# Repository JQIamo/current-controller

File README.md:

# Low noise current controller

Gerber files for a low-noise current controller, based on the design from the Durfee lab. [DOI:10.1063/1.2953597](http://scitation.aip.org/content/aip/journal/rsi/79/7/10.1063/1.2953597)

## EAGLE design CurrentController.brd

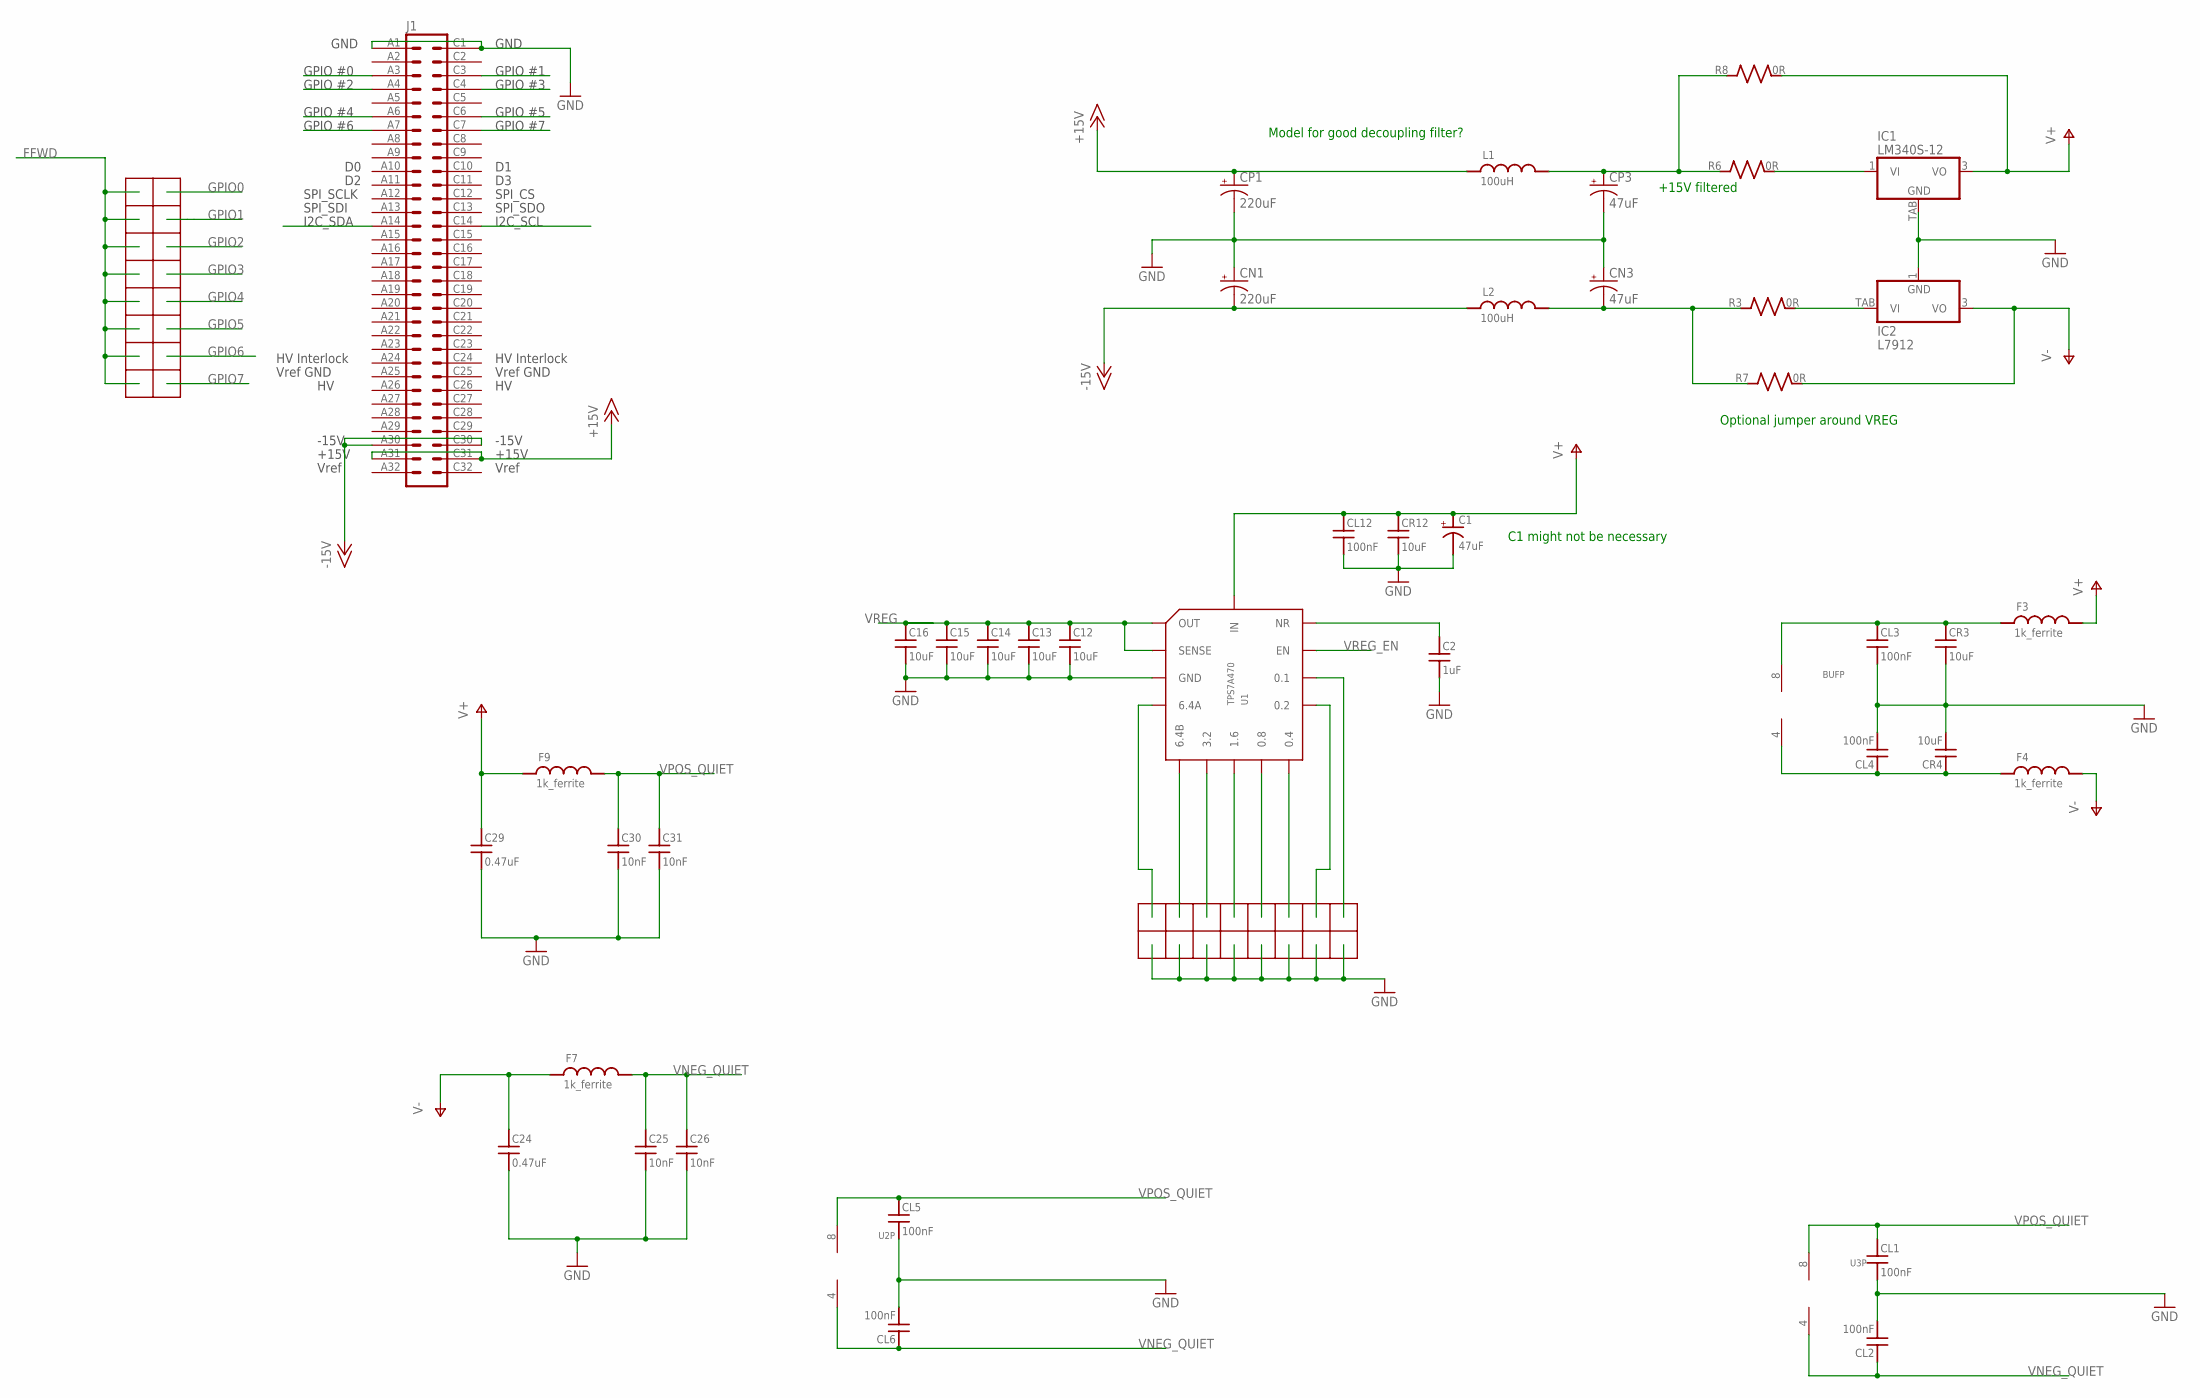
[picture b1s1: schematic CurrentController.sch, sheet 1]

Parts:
BUF: AD8676; MSOP08; PARTNO AD8676ARMZ
C1: 47uF; C_POL_1206
C2: 1uF; C_MLCC_0603; PARTNO CL10B105KA8NNNC
C12, C13, C14, C15, C16: 10uF; C_MLCC_0805; PARTNO CL21A106KAFN3NE
C24, C29: 0.47uF; C_MLCC_0612; PARTNO LLL31MR71E474MA01L
C25, C26, C30, C31: 10nF; C_MLCC_0306; PARTNO 03063C103KAT2A
CL1, CL2, CL3, CL4, CL5, CL6, CL12: 100nF; C_MLCC_0603; PARTNO C1608X7R1E104K080AA
CN1: 220uF; PANASONIC_F; PARTNO EEE-1VA221UP
CN3: 47uF; CT7343; PARTNO T491D476M025AT
CP1: 220uF; PANASONIC_F; PARTNO EEE-1VA221UP
CP3: 47uF; CT7343; PARTNO T491D476M025AT
CR3, CR4, CR12: 10uF; C_MLCC_0805; PARTNO CL21A106KAFN3NE
F3, F4, F7, F9: 1k_ferrite; L_FERRITE_0603; PARTNO BLM18HG102SN1D
IC1: LM340S-12; TO263-3; PARTNO LM340S-12/NOPB
IC2: L7912; TO223-3; PARTNO MC7912CD2TG
J1: VG64C; VG64-CUTOUT; PARTNO 5650945-5
J2, J3: 2X8_LOW_PROFILE_JUMPER; 2X8_LOW_PROFILE_JUMPER_MATRIX; PARTNO A3B-16PA-2DSA(71)
L1, L2: 100uH; WURTH_1280; PARTNO 74477020
R3, R6, R7, R8: 0R; R_1206; PARTNO ERJ-8GEY0R00V
U1: TPS7A470; S-PVQFN-N20; PARTNO TPS7A4701RGWT
U2, U3: AD8676; MSOP08; PARTNO AD8676ARMZ

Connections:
+15V: CP1.+, J1.A31, J1.C31, L1.P$1 (1)
-15V: CN1.-, J1.A30, J1.C30, L2.P$1 (1)
FFWD: J2.P$1, J2.P$3, J2.P$5, J2.P$7, J2.P$9, J2.P$11, J2.P$13, J2.P$15; also elsewhere on the board
GND: C1.P$2 (-), C2.P$2 (2), C12.P$2 (2), C13.P$2 (2), C14.P$2 (2), C15.P$2 (2), C16.P$2 (2), C24.P$2 (2), C25.P$2 (2), C26.P$2 (2), C29.P$2 (2), C30.P$2 (2), C31.P$2 (2), CL1.P$2 (2), CL2.P$2 (2), CL3.P$2 (2), CL4.P$2 (2), CL5.P$2 (2), CL6.P$2 (2), CL12.P$2 (2), CN1.+, CN3.+, CP1.-, CP3.-, CR3.P$2 (2), CR4.P$2 (2), CR12.P$2 (2), IC1.TAB (GND), IC2.1 (GND), J1.A1, J1.C1, J3.P$1, J3.P$3, J3.P$5, J3.P$7, J3.P$9, J3.P$11, J3.P$13, J3.P$15, U1.2 (GND), U1.7 (GND), U1.17 (GND), U1.18 (GND), U1.19 (GND), U1.EXP (GND); also elsewhere on the board
GPIO0: J1.A3, J2.P$2
GPIO1: J1.C3, J2.P$4
GPIO2: J1.A4, J2.P$6
GPIO3: J1.C4, J2.P$8
GPIO4: J1.A6, J2.P$10
GPIO5: J1.C6, J2.P$12
GPIO6: J1.A7, J2.P$14
GPIO7: J1.C7, J2.P$16
unnamed: J3.P$2, U1.4 (6.4A)
unnamed: IC2.TAB (VI), R3.P$2 (2)
unnamed: IC1.1 (VI), R6.P$2 (2)
unnamed: J3.P$4, U1.5 (6.4B)
unnamed: CN3.-, L2.P$2 (2), R3.P$1 (1), R7.P$1 (1)
unnamed: J3.P$6, U1.6 (3.2)
unnamed: CP3.+, L1.P$2 (2), R6.P$1 (1), R8.P$1 (1)
unnamed: J3.P$8, U1.8 (1.6)
unnamed: BUF.4 (V-), CL4.P$1 (1), CR4.P$1 (1), F4.P$1 (1)
unnamed: BUF.8 (V+), CL3.P$1 (1), CR3.P$1 (1), F3.P$1 (1)
unnamed: J3.P$10, U1.9 (0.8)
unnamed: J3.P$12, U1.10 (0.4)
unnamed: J3.P$14, U1.11 (0.2)
unnamed: J3.P$16, U1.12 (0.1)
unnamed: C2.P$1 (1), U1.14 (NR)
SCL: J1.C14; also elsewhere on the board
SDA: J1.A14; also elsewhere on the board
V+: C1.P$1 (+), C29.P$1 (1), CL12.P$1 (1), CR12.P$1 (1), F3.P$2 (2), F9.P$1 (1), IC1.3 (VO), R8.P$2 (2), U1.15 (IN), U1.16 (IN); also elsewhere on the board
V-: C24.P$1 (1), F4.P$2 (2), F7.P$1 (1), IC2.3 (VO), R7.P$2 (2); also elsewhere on the board
VNEG_QUIET: C25.P$1 (1), C26.P$1 (1), CL2.P$1 (1), CL6.P$1 (1), F7.P$2 (2), U2.4 (V-), U3.4 (V-); also elsewhere on the board
VPOS_QUIET: C30.P$1 (1), C31.P$1 (1), CL1.P$1 (1), CL5.P$1 (1), F9.P$2 (2), U2.8 (V+), U3.8 (V+); also elsewhere on the board
VREG: C12.P$1 (1), C13.P$1 (1), C14.P$1 (1), C15.P$1 (1), C16.P$1 (1), U1.1 (OUT), U1.3 (SENSE), U1.20 (OUT); also elsewhere on the board
VREG_EN: U1.13 (EN); also elsewhere on the board

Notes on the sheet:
+15V filtered
Optional jumper around VREG
Model for good decoupling filter?
C1 might not be necessary

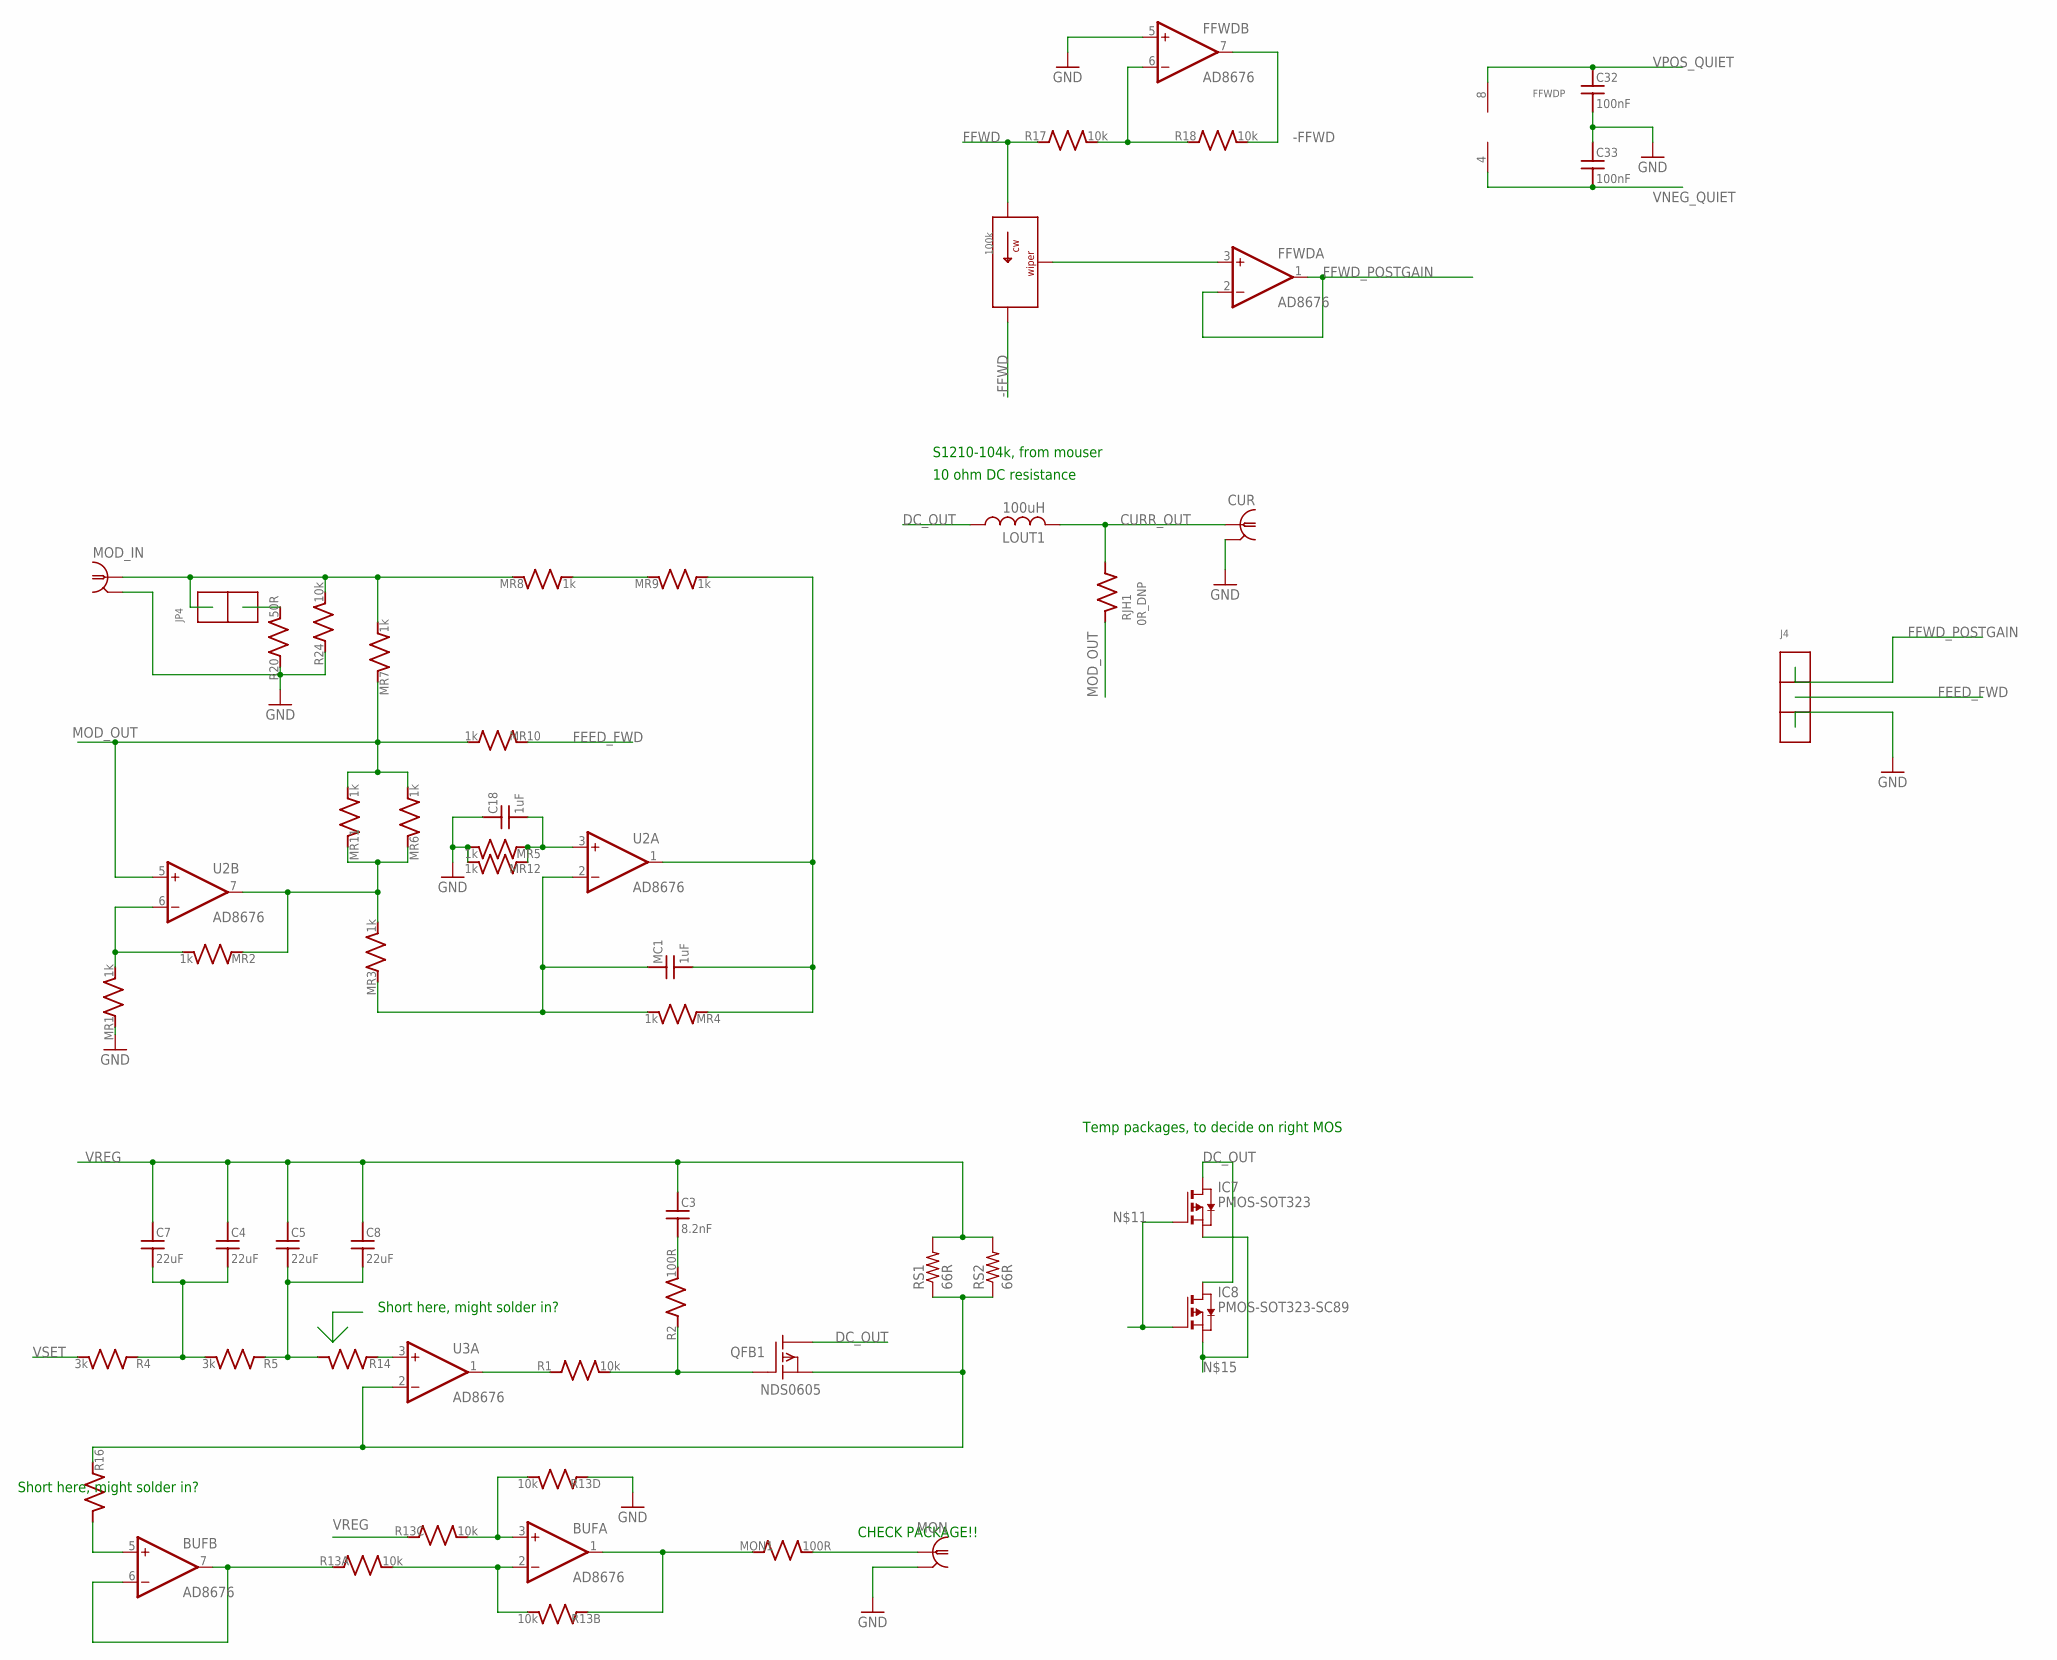
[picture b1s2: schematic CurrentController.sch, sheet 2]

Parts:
BUF: AD8676; MSOP08; PARTNO AD8676ARMZ
C3: 8.2nF; C_MLCC_0603; PARTNO CL10B822KB8NNNC
C4, C5, C7, C8: 22uF; C_MLCC_0805; PARTNO C2012X5R1E226M125AC
C18: 1uF; C_MLCC_0603; PARTNO CL10B105KA8NNNC
C32, C33: 100nF; C_MLCC_0603; PARTNO C1608X7R1E104K080AA
CUR: BNC-H; BNC90; PARTNO 5227161-7
FFWD: AD8676; MSOP08; PARTNO AD8676ARMZ
IC7: PMOS-SOT323; SOT323
IC8: PMOS-SOT323-SC89; SC-89
J4: 1X3_LOW_PROFILE_JUMPER; 1X3_LOW_PROFILE; PARTNO NRPN031PAEN-RC
JP4: 1X2_LOW_PROFILE_JUMPER; 1X2_LOW_PROFILE; PARTNO NRPN021PAEN-RC
LOUT1: 100uH; L3225P; PARTNO CBC3225T680KR
MC1: 1uF; C_MLCC_0603; PARTNO CL10B105KA8NNNC
MOD_IN: BNC-H; BNC90; PARTNO 5227161-7
MON: UMC; PARTNO 1909763-1
MON1: 100R; R_0603; PARTNO ERJ-3EKF1000V
MR1, MR2, MR3, MR4, MR5, MR6, MR7, MR8, MR9, MR10, MR11, MR12: 1k; R_0805; PARTNO ERA-6ARB102V
QFB1: NDS0605; SOT-23; PARTNO *
R1, R17, R18, R24: 10k; R_0603; PARTNO ERJ-3EKF1002V
R2: 100R; R_0603; PARTNO ERJ-3EKF1000V
R4, R5: 3k; R_0603; PARTNO ERJ-3EKF3001V
R13: 10k; 742_ARRAY; PARTNO 742C083103JP
R14, R16: R_SMDR0603; R_0603
R20: 50R; R_0805; PARTNO ERJ-6ENF49R9V
RJH1: 0R_DNP; R_0603
RS1, RS2: 66R; R2010
T1: 100k; 3006P; PARTNO 3006P-1-104LF
U2, U3: AD8676; MSOP08; PARTNO AD8676ARMZ

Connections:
-FFWD: FFWD.7 (OUT), R18.P$2 (2), T1.P$3
CURR_OUT: CUR.1, LOUT1.2, RJH1.P$1 (1)
DC_OUT: IC7.3 (D), IC8.P$3 (D), LOUT1.1, QFB1.3 (D)
FEED_FWD: J4.P2, MR10.P$1 (1)
FFWD: R17.P$1 (1), T1.P$1; also elsewhere on the board
FFWD_POSTGAIN: FFWD.1 (OUT), FFWD.2 (-IN), J4.P1
GND: C18.P$1 (1), C32.P$2 (2), C33.P$1 (1), CUR.2, FFWD.5 (+IN), J4.P3, MOD_IN.2, MON.P$2 (2), MON.P$3 (2), MR1.P$1 (1), MR5.P$2 (2), MR12.P$2 (2), R13.P$7 (1), R20.P$1 (1), R24.P$1 (1); also elsewhere on the board
MODIN_B: JP4.1, MOD_IN.1, MR7.P$2 (2), MR8.P$1 (1), R24.P$2 (2)
MOD_OUT: MR6.P$2 (2), MR7.P$1 (1), MR10.P$2 (2), MR11.P$2 (2), RJH1.P$2 (2), U2.5 (+IN)
MON: BUF.1 (OUT), MON1.P$1 (1), R13.P$3 (1)
MON_MON: MON.P$1 (1), MON1.P$2 (2)
unnamed: MR8.P$2 (2), MR9.P$1 (1)
unnamed: BUF.6 (-IN), BUF.7 (OUT), R13.P$1 (1)
unnamed: BUF.5 (+IN), R16.P$2 (2)
unnamed: FFWD.3 (+IN), T1.P$2
unnamed: C4.P$2 (2), C7.P$2 (2), R4.P$1 (1), R5.P$2 (2)
unnamed: C5.P$2 (2), C8.P$2 (2), R5.P$1 (1), R14.P$2 (2)
unnamed: R1.P$1 (1), U3.1 (OUT)
unnamed: IC7.1 (G), IC8.P$1 (G), QFB1.1 (G), R1.P$2 (2), R2.P$1 (1)
unnamed: R14.P$1 (1), U3.3 (+IN)
unnamed: C3.P$2 (2), R2.P$2 (2)
unnamed: BUF.2 (-IN), R13.P$2 (2), R13.P$4 (2)
unnamed: IC7.2 (S), IC8.P$2 (S), QFB1.2 (S), R16.P$1 (1), RS1.1, RS2.1, U3.2 (-IN)
unnamed: BUF.3 (+IN), R13.P$6 (2), R13.P$8 (2)
unnamed: MR1.P$2 (2), MR2.P$2 (2), U2.6 (-IN)
unnamed: MR2.P$1 (1), MR3.P$2 (2), MR6.P$1 (1), MR11.P$1 (1), U2.7 (OUT)
unnamed: C18.P$2 (2), MR5.P$1 (1), MR12.P$1 (1), U2.3 (+IN)
unnamed: MC1.P$2 (2), MR4.P$1 (1), MR9.P$2 (2), U2.1 (OUT)
unnamed: MC1.P$1 (1), MR3.P$1 (1), MR4.P$2 (2), U2.2 (-IN)
unnamed: JP4.2, R20.P$2 (2)
unnamed: FFWD.6 (-IN), R17.P$2 (2), R18.P$1 (1)
VNEG_QUIET: C33.P$2 (2), FFWD.4 (V-); also elsewhere on the board
VPOS_QUIET: C32.P$1 (1), FFWD.8 (V+); also elsewhere on the board
VREG: C3.P$1 (1), C4.P$1 (1), C5.P$1 (1), C7.P$1 (1), C8.P$1 (1), R13.P$5 (1), RS1.2, RS2.2; also elsewhere on the board
VSET: R4.P$2 (2); also elsewhere on the board

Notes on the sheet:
S1210-104k, from mouser
10 ohm DC resistance
Short here, might solder in?
CHECK PACKAGE!!
Temp packages, to decide on right MOS

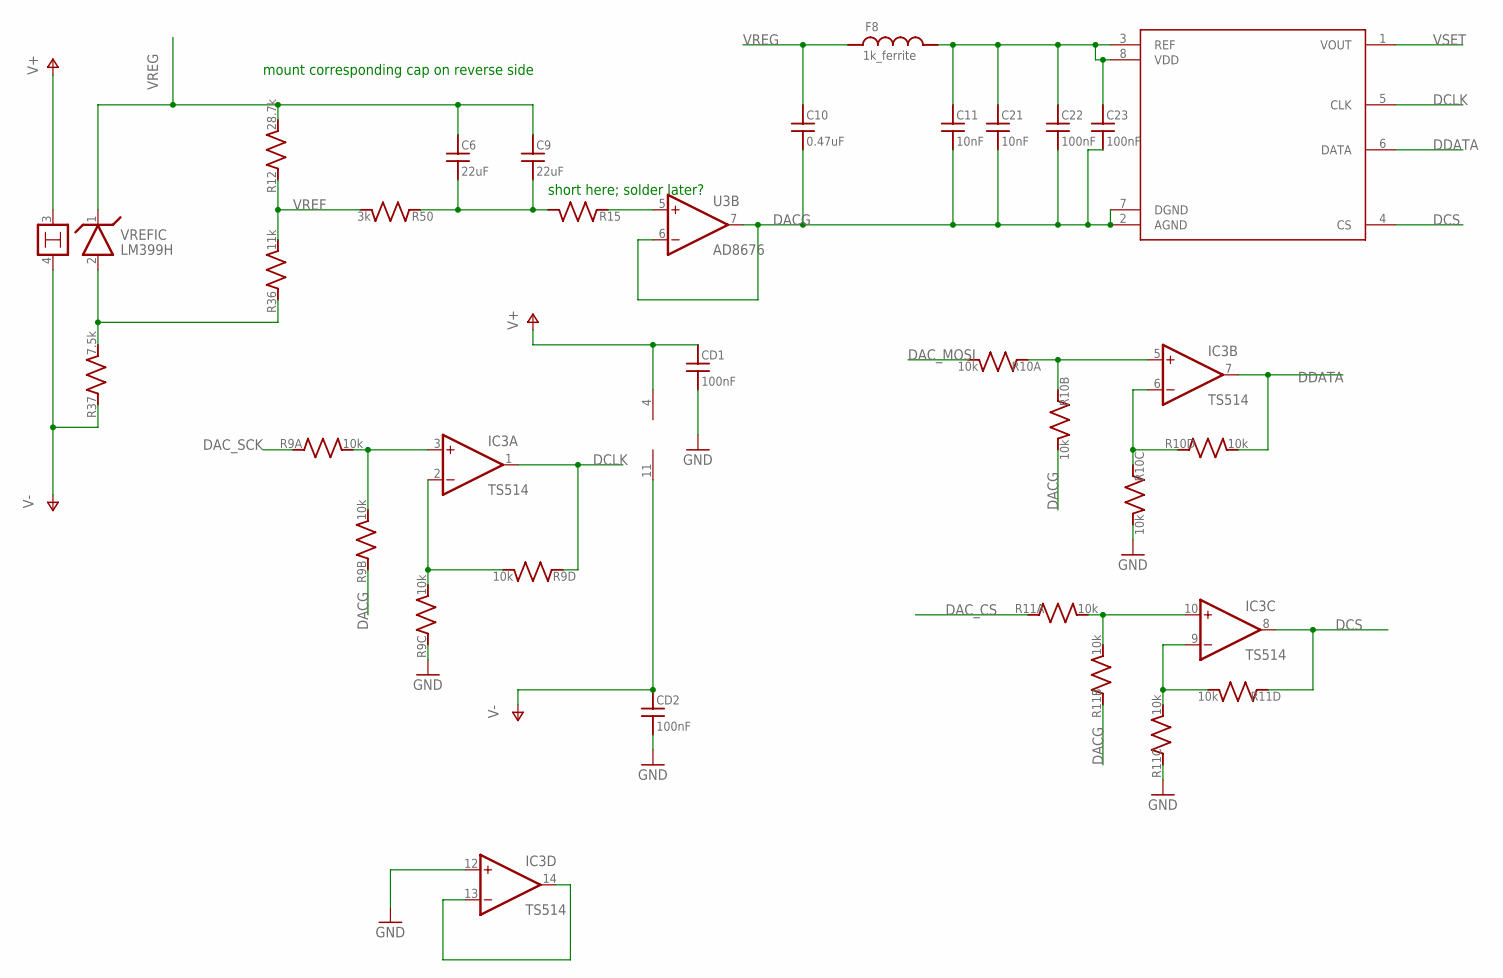
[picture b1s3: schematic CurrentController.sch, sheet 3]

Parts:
C6, C9: 22uF; C_MLCC_0805; PARTNO C2012X5R1E226M125AC
C10: 0.47uF; C_MLCC_0612; PARTNO LLL31MR71E474MA01L
C11, C21: 10nF; C_MLCC_0306; PARTNO 03063C103KAT2A
C22, C23: 100nF; C_MLCC_0603; PARTNO C1608X7R1E104K080AA
CD1, CD2: 100nF; C_MLCC_0603; PARTNO C1608X7R1E104K080AA
DAC1: AD5541; SOIC-8; PARTNO AD5541BRZ
F8: 1k_ferrite; L_FERRITE_0603; PARTNO BLM18HG102SN1D
IC3: TS514; SO14; PARTNO TS514AIDT
R9, R10, R11: 10k; 742_ARRAY; PARTNO 742C083103JP
R12: 28.7k; R_0603; PARTNO ERJ-3EKF2872V
R15: R_SMDR0603; R_0603
R36: 11k; R_0603; PARTNO ERJ-3EKF1102V
R37: 7.5k; R_0603; PARTNO ERJ-3EKF7501V
R50: 3k; R_0603; PARTNO ERJ-3EKF3001V
U3: AD8676; MSOP08; PARTNO AD8676ARMZ
VREFIC: LM399H; TO39/4; PARTNO LM399H#PBF

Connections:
DACG: C10.P$2 (2), C11.P$2 (2), C21.P$2 (2), C22.P$2 (2), C23.P$2 (2), DAC1.2 (AGND), DAC1.7 (DGND), R9.P$3 (1), R10.P$4 (2), R11.P$3 (1), U3.6 (-IN), U3.7 (OUT)
DAC_CS: R11.P$1 (1); also elsewhere on the board
DAC_MOSI: R10.P$2 (2); also elsewhere on the board
DAC_SCK: R9.P$1 (1); also elsewhere on the board
DCLK: DAC1.5 (CLK), IC3.1 (OUT), R9.P$7 (1)
DCS: DAC1.4 (CS), IC3.8 (OUT), R11.P$7 (1)
DDATA: DAC1.6 (DATA), IC3.7 (OUT), R10.P$8 (2)
GND: CD1.P$2 (2), CD2.P$2 (2), IC3.12 (+IN), R9.P$5 (1), R10.P$6 (2), R11.P$5 (1); also elsewhere on the board
unnamed: IC3.9 (-IN), R11.P$6 (2), R11.P$8 (2)
unnamed: IC3.2 (-IN), R9.P$6 (2), R9.P$8 (2)
unnamed: R36.P$1 (1), R37.P$2 (2), VREFIC.2
unnamed: R15.P$1 (1), U3.5 (+IN)
unnamed: IC3.3 (+IN), R9.P$2 (2), R9.P$4 (2)
unnamed: IC3.5 (+IN), R10.P$1 (1), R10.P$3 (1)
unnamed: IC3.6 (-IN), R10.P$5 (1), R10.P$7 (1)
unnamed: C6.P$2 (2), C9.P$2 (2), R15.P$2 (2), R50.P$1 (1)
unnamed: IC3.10 (+IN), R11.P$2 (2), R11.P$4 (2)
unnamed: IC3.13 (-IN), IC3.14 (OUT)
V+: CD1.P$1 (1), IC3.4 (V+), VREFIC.3; also elsewhere on the board
V-: CD2.P$1 (1), IC3.11 (V-), R37.P$1 (1), VREFIC.4; also elsewhere on the board
VREF: R12.P$1 (1), R36.P$2 (2), R50.P$2 (2)
VREG: C6.P$1 (1), C9.P$1 (1), C10.P$1 (1), F8.P$1 (1), R12.P$2 (2), VREFIC.1; also elsewhere on the board
VREG_DAC: C11.P$1 (1), C21.P$1 (1), C22.P$1 (1), C23.P$1 (1), DAC1.3 (REF), DAC1.8 (VDD), F8.P$2 (2)
VSET: DAC1.1 (VOUT); also elsewhere on the board

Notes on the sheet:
mount corresponding cap on reverse side
short here; solder later?

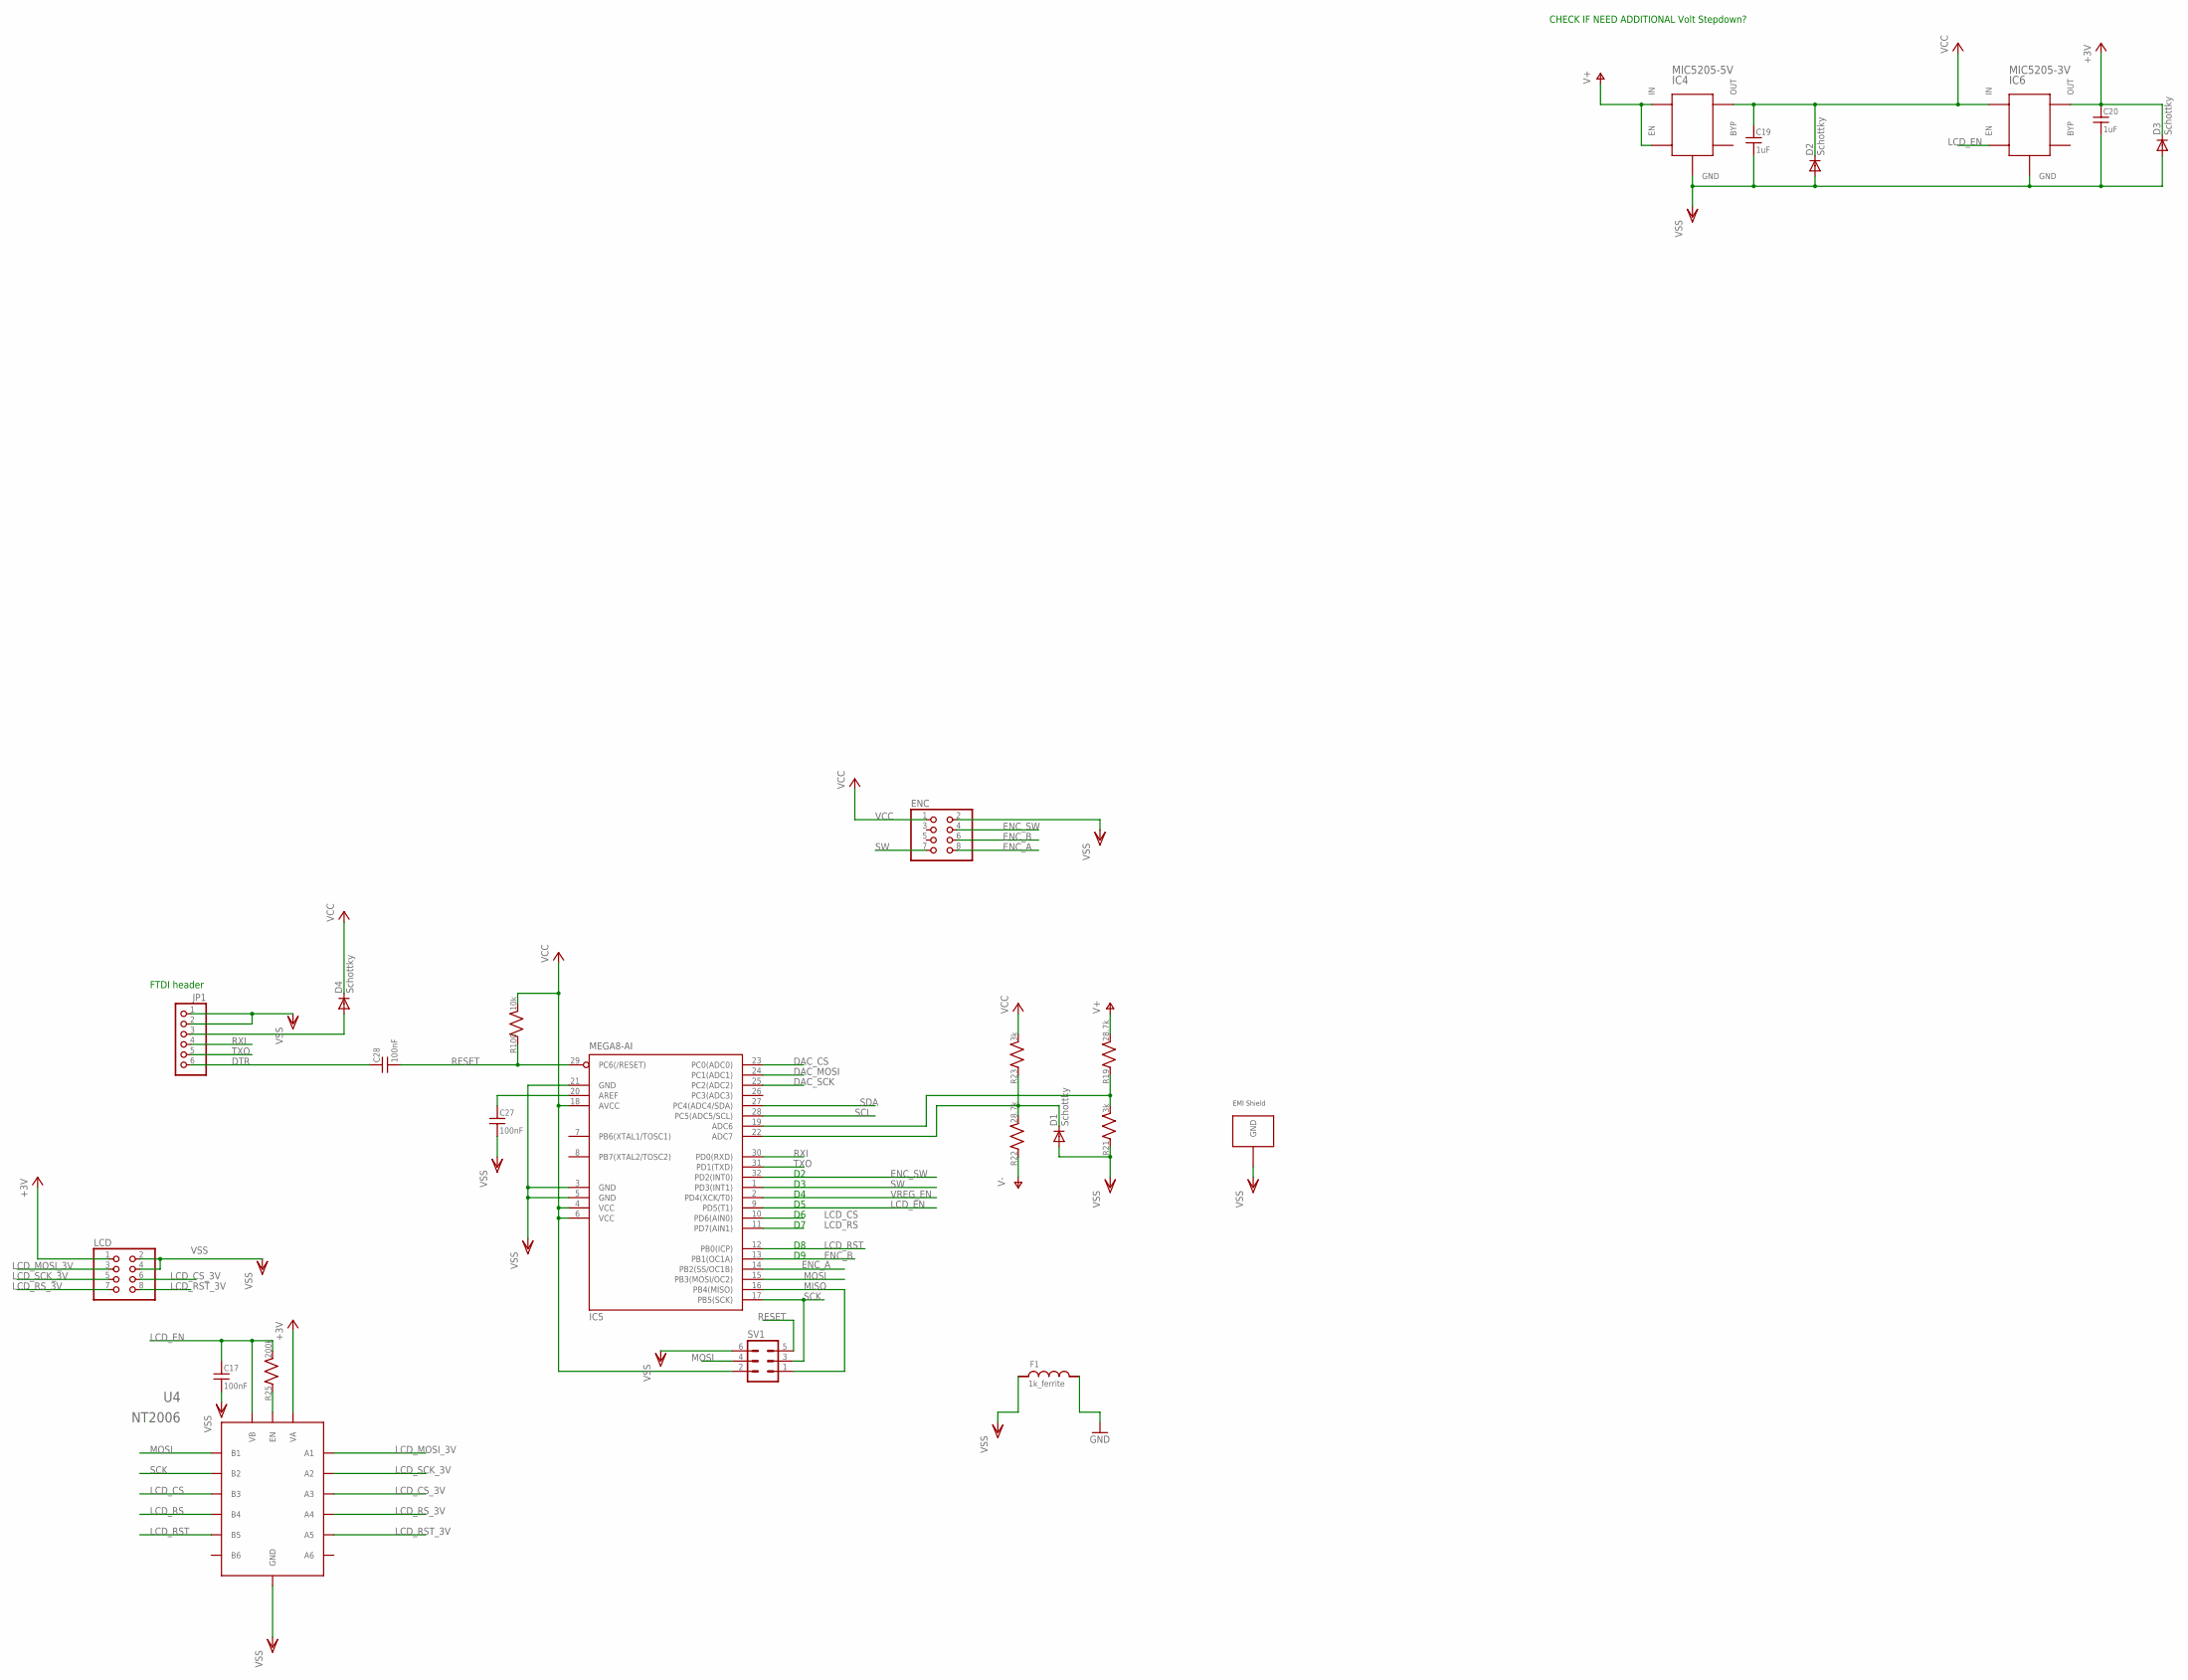
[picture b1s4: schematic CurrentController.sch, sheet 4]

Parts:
C17, C27, C28: 100nF; C_MLCC_0603; PARTNO C1608X7R1E104K080AA
C19, C20: 1uF; C_MLCC_0603; PARTNO CL10B105KA8NNNC
D1, D2, D3, D4: Schottky; SOD523; PARTNO PMEG3005EB,115
ENC: PINHD-2X4-SHROUD; ML08; PARTNO 75869-132LF
F1: 1k_ferrite; L_FERRITE_0603; PARTNO BLM18HG102SN1D
IC4: MIC5205-5V; SOT23-5L; PARTNO MIC5205-5.0YM5-TR
IC5: MEGA8-AI; TQFP32-08; PARTNO ATMEGA328P-AU
IC6: MIC5205-3V; SOT23-5L; PARTNO MIC5205-3.0YM5-TR
JP1: PINHD-1X6; 1X06; PARTNO 68000-406HLF
LCD: PINHD-2X4-SHROUD; ML08; PARTNO 75869-132LF
R19, R22: 28.7k; R_0603; PARTNO ERJ-3EKF2872V
R21, R23: 3k; R_0603; PARTNO ERJ-3EKF3001V
R25: 200k; R_0603; PARTNO ERJ-3EKF2003V
R100: 10k; R_0603; PARTNO ERJ-3EKF1002V
SV1: MA03-2; PARTNO 67996-406HLF
U4: NT2006; HVQFN16; PARTNO NVT2006BS,118
U$5: WURTH_EMI; WURTH_SHIELD; PARTNO 36103205

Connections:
+3V: C20.P$1 (1), D3.C, IC6.5 (OUT), LCD.1, U4.16 (VA)
A6: IC5.19 (ADC6), R19.P$1 (1), R21.P$2 (2)
A7: D1.C, IC5.22 (ADC7), R22.P$2 (2), R23.P$1 (1)
DAC_CS: IC5.23 (PC0(ADC0)); also elsewhere on the board
DAC_MOSI: IC5.24 (PC1(ADC1)); also elsewhere on the board
DAC_SCK: IC5.25 (PC2(ADC2)); also elsewhere on the board
DTR: C28.P$1 (1), JP1.6
ENC_A: ENC.8, IC5.14 (PB2(SS/OC1B))
ENC_B: ENC.6, IC5.13 (PB1(OC1A))
ENC_SW: ENC.4, IC5.32 (PD2(INT0))
GND: F1.P$2 (2); also elsewhere on the board
LCD_CS: IC5.10 (PD6(AIN0)), U4.10 (B3)
LCD_CS_3V: LCD.6, U4.3 (A3)
LCD_EN: C17.P$1 (1), IC5.9 (PD5(T1)), IC6.3 (EN), R25.P$2 (2), U4.13 (VB)
LCD_MOSI_3V: LCD.3, U4.1 (A1)
LCD_RS: IC5.11 (PD7(AIN1)), U4.9 (B4)
LCD_RST: IC5.12 (PB0(ICP)), U4.8 (B5)
LCD_RST_3V: LCD.8, U4.5 (A5)
LCD_RS_3V: LCD.7, U4.4 (A4)
LCD_SCK_3V: LCD.5, U4.2 (A2)
MISO: IC5.16 (PB4(MISO)), SV1.1
MOSI: IC5.15 (PB3(MOSI/OC2)), SV1.4, U4.12 (B1)
unnamed: D4.A, JP1.3
unnamed: C27.P$1 (1), IC5.20 (AREF)
unnamed: R25.P$1 (1), U4.14 (EN)
RESET: C28.P$2 (2), IC5.29 (PC6(/RESET)), R100.P$1 (1), SV1.5
RXI: IC5.30 (PD0(RXD)), JP1.4
SCK: IC5.17 (PB5(SCK)), SV1.3, U4.11 (B2)
SCL: IC5.28 (PC5(ADC5/SCL)); also elsewhere on the board
SDA: IC5.27 (PC4(ADC4/SDA)); also elsewhere on the board
SW: ENC.7, IC5.1 (PD3(INT1))
TXO: IC5.31 (PD1(TXD)), JP1.5
V+: IC4.1 (IN), IC4.3 (EN), R19.P$2 (2); also elsewhere on the board
V-: R22.P$1 (1); also elsewhere on the board
VCC: C19.P$1 (1), D2.C, D4.C, ENC.1, IC4.5 (OUT), IC5.4 (VCC), IC5.6 (VCC), IC5.18 (AVCC), IC6.1 (IN), R23.P$2 (2), R100.P$2 (2), SV1.2
VREG_EN: IC5.2 (PD4(XCK/T0)); also elsewhere on the board
VSS: C17.P$2 (2), C19.P$2 (2), C20.P$2 (2), C27.P$2 (2), D1.A, D2.A, D3.A, ENC.2, F1.P$1 (1), IC4.2 (GND), IC5.3 (GND), IC5.5 (GND), IC5.21 (GND), IC6.2 (GND), JP1.1, JP1.2, LCD.2, LCD.4, R21.P$1 (1), SV1.6, U4.15 (GND), U4.P$17 (GND), U$5.P$1, U$5.P$2, U$5.P$3, U$5.P$4, U$5.P$5, U$5.P$6, U$5.P$7, U$5.P$8, U$5.P$9, U$5.P$10, U$5.P$11, U$5.P$12, U$5.P$13, U$5.P$14, U$5.P$15, U$5.P$16

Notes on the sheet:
FTDI header
CHECK IF NEED ADDITIONAL Volt Stepdown?

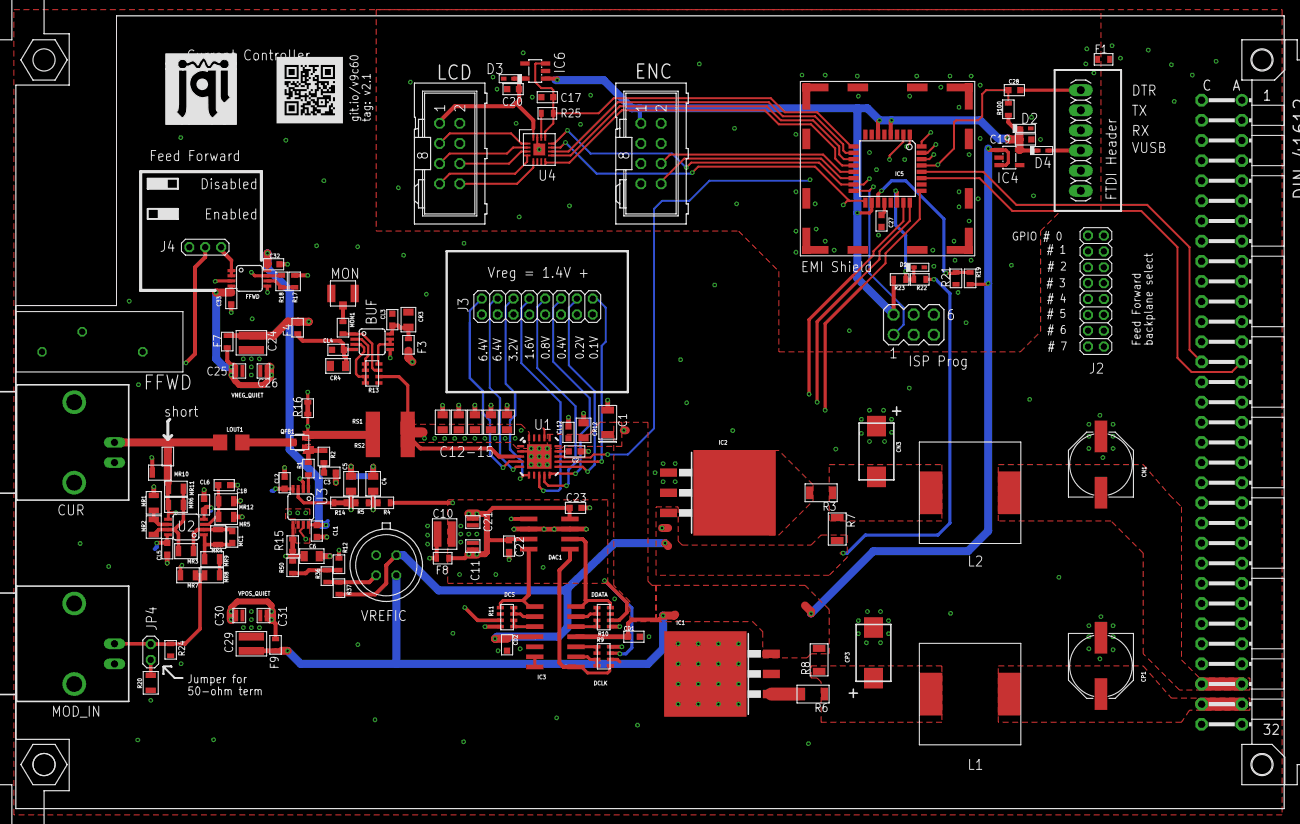
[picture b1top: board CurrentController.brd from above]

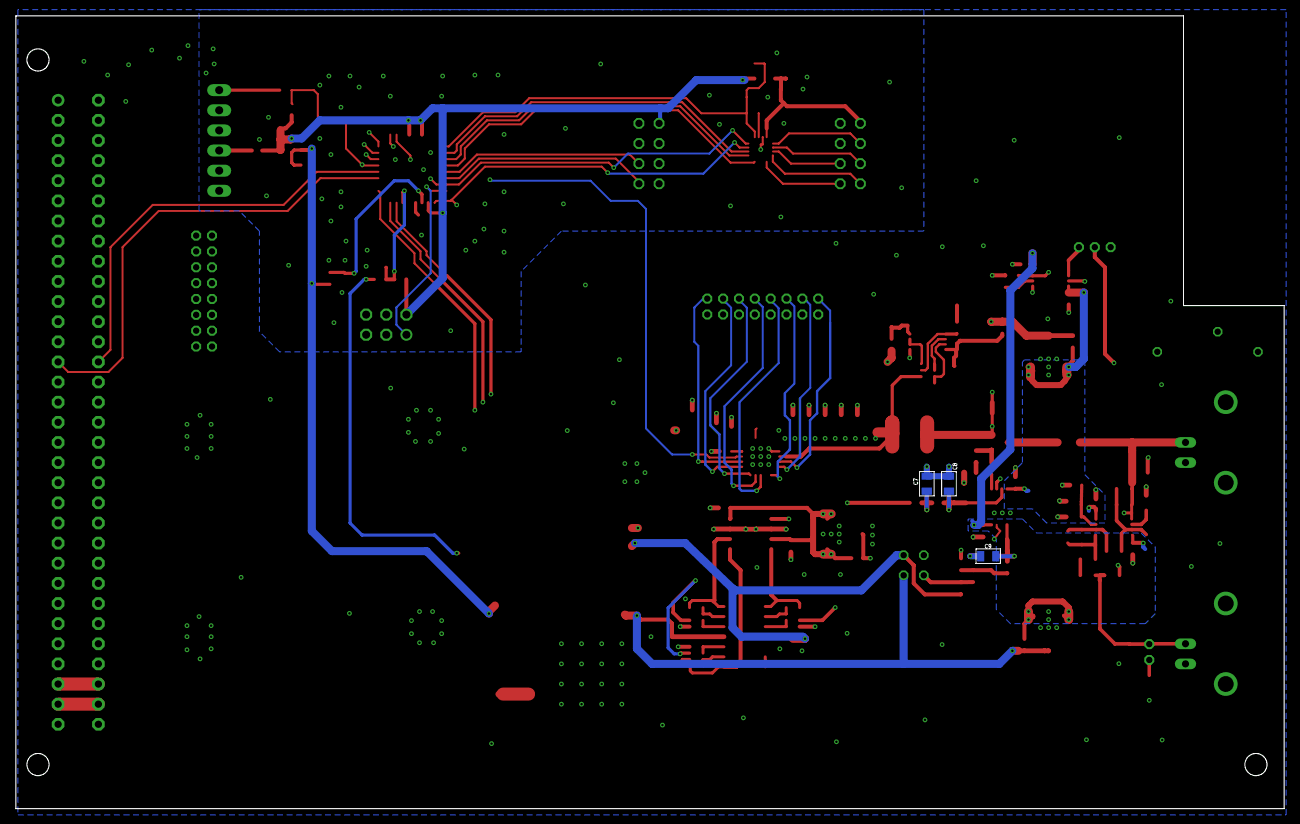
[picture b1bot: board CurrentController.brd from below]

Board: 4 copper layers, 160.0 x 100.0 mm, 141 parts (3 on the bottom side), 112 nets.

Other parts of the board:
U$4: JQI_LOGO_NEGATIVE-SILKSCREEN
U$6: QR-HTTPS://GIT.IO/V9C60-LIGHT-SILK

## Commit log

2015-06-23 Added v1.0, screaming circuits order information
2015-06-23 Leaving gerbers included in repo, for ease of re-ordering boards
2015-06-23 Added in gerbers for v1.0
2015-06-23 Added a readme
2015-07-16 Added DOI reference to Durfee current controller
    RSI paper reference
2015-07-18 Added part number attributes file
2015-07-18 Working on re-routing; about to add feed forward
2015-10-12 mostly routed, few remaining tweaks
2015-12-08 final routing and gerbers for v2
2016-01-31 Added durfee current controller schematic, for posterity
2017-03-22 Mostly working code for v2.0 hardware
2017-03-22 removed upload target in makefile
2017-03-23 Working sketch although max menu not working
2017-05-25 Updated silkscreen; other minor mods
    Prepping for fabrication at macrofab.
2017-06-12 added xyrs file for macrofab
2017-07-21 v2 working but not field tested
2017-07-21 ammended makefile
2017-08-24 added noise PSD trace
2017-08-24 code commit
2017-08-24 switched license to CERN OHWL v1.2
2018-07-10 added a script to program the microcontroller with avrdude and buspirate
2019-09-16 added missing gerber *.crs file for solder paste bottom
